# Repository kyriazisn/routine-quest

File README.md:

# Routine Quest

Παιδικό device (4 φυσικά κουμπιά, ESP32-S3, Wi-Fi) που μετατρέπει τις καθημερινές ρουτίνες σε quests και ειδοποιεί τον γονέα.

## Δομή

| Φάκελος | Περιεχόμενο |
|---|---|
| `docs/` | Product brief, game design, test plan, risks |
| `firmware/` | ESP32-S3 firmware (ESP-IDF) |
| `backend/` | FastAPI + Postgres, device & parent API, Web Push |
| `app/` | Parent PWA |
| `hardware/` | KiCad schematic, BOM, PCB |

## Ροή εργασίας

- Κάθε αλλαγή σε ξεχωριστό branch → PR → review → merge στο `main`.
- Κανένα direct commit στο `main` μετά το initial scaffold.
- Το PCB layout ξεκινά **μόνο** μετά από έγκριση του schematic.

## Φάσεις

1. Product brief & user stories — `docs/01-product-brief.md`
2. Game loop, XP, streaks, rewards — `docs/02-game-design.md`
3. Wireframes (Figma)
4. Firmware — `firmware/`
5. Backend & notifications — `docs/05-backend.md`
6. Schematic → (έγκριση) → PCB — `docs/06-hardware.md`
6.5. Parent PWA: υλοποίηση των wireframes, Web Push, BLE provisioning + claim (`app/`)
7. Test plan (end-to-end: device + backend + PWA)
8. Landing page & launch
9. Risks, safety, privacy, parental controls

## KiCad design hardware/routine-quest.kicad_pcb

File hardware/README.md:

# Routine Quest — Hardware

Design notes, calculations and the approval checklist: [`docs/06-hardware.md`](../docs/06-hardware.md).

> **Status:** schematic v0.1 approved (2026-10-13). PCB layout (Phase 6b) **in progress, not for ordering** — see [`docs/06b-pcb.md`](../docs/06b-pcb.md).

## Files

| Path | |
|---|---|
| `routine-quest.kicad_pro` / `routine-quest.kicad_sch` | Main board |
| `button-board/button-board.kicad_sch` | Button board (×4) |
| `bom/*.csv` | Bill of materials |
| `build/*.pdf` | Review renders (generated, not committed — see CI artifact) |
| `build/*.netlist.json` | Reviewed netlist, checked against the schematic |
| `tools/gen_schematics.py` | **Source of truth.** Edit this, not the `.kicad_sch` |
| `tools/check_schematic.py` | Independent connectivity + ERC-style checks |
| `tools/render_schematic.py` | PDF/PNG render without KiCad |

## Regenerate & check

```bash
git clone https://github.com/espressif/kicad-libraries.git /tmp/esplib   # pinned SHA in .github/workflows/hardware.yml
pip install kiutils==1.4.8 matplotlib
ESP_KICAD_LIB=/tmp/esplib/symbols/Espressif.kicad_sym python hardware/tools/gen_schematics.py
python hardware/tools/check_schematic.py
python hardware/tools/render_schematic.py
```

Then run KiCad's own ERC (`kicad-cli sch erc`) — see docs/06 §7.

## Licences

The ESP32-S3-WROOM-1 symbol embedded in the schematic comes from
[espressif/kicad-libraries](https://github.com/espressif/kicad-libraries) (CC-BY-SA 4.0 with the KiCad library
exception for designs).

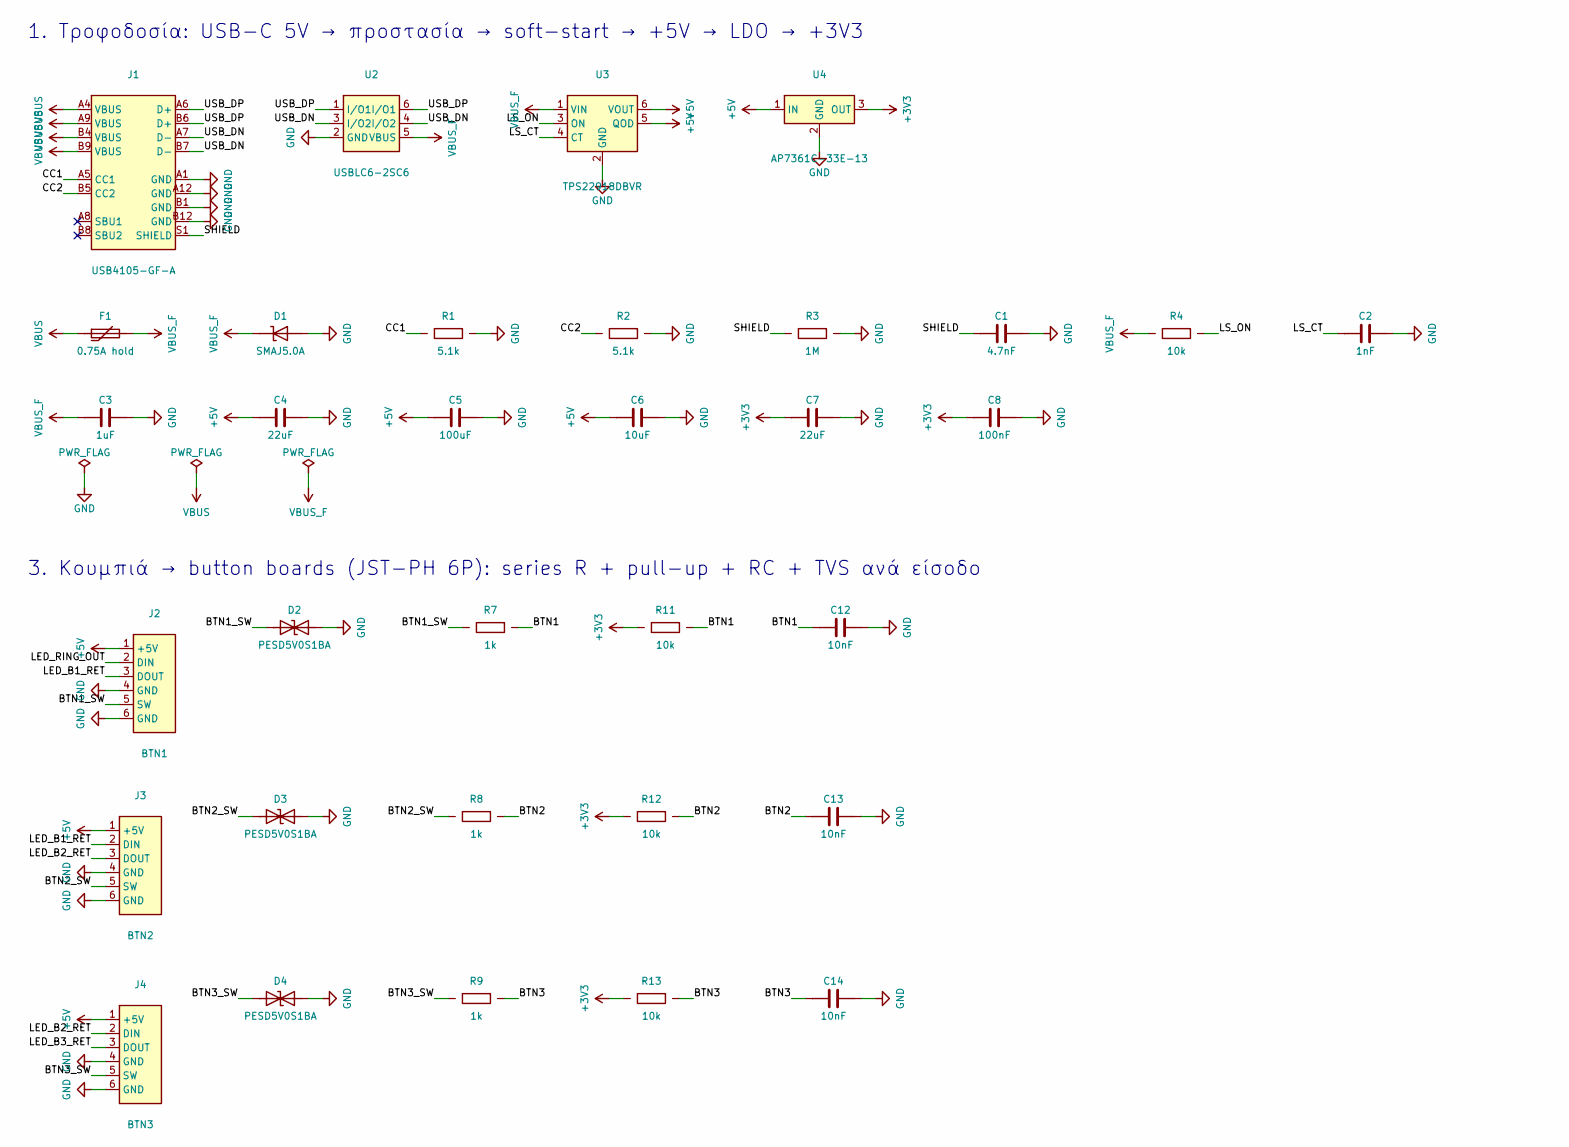
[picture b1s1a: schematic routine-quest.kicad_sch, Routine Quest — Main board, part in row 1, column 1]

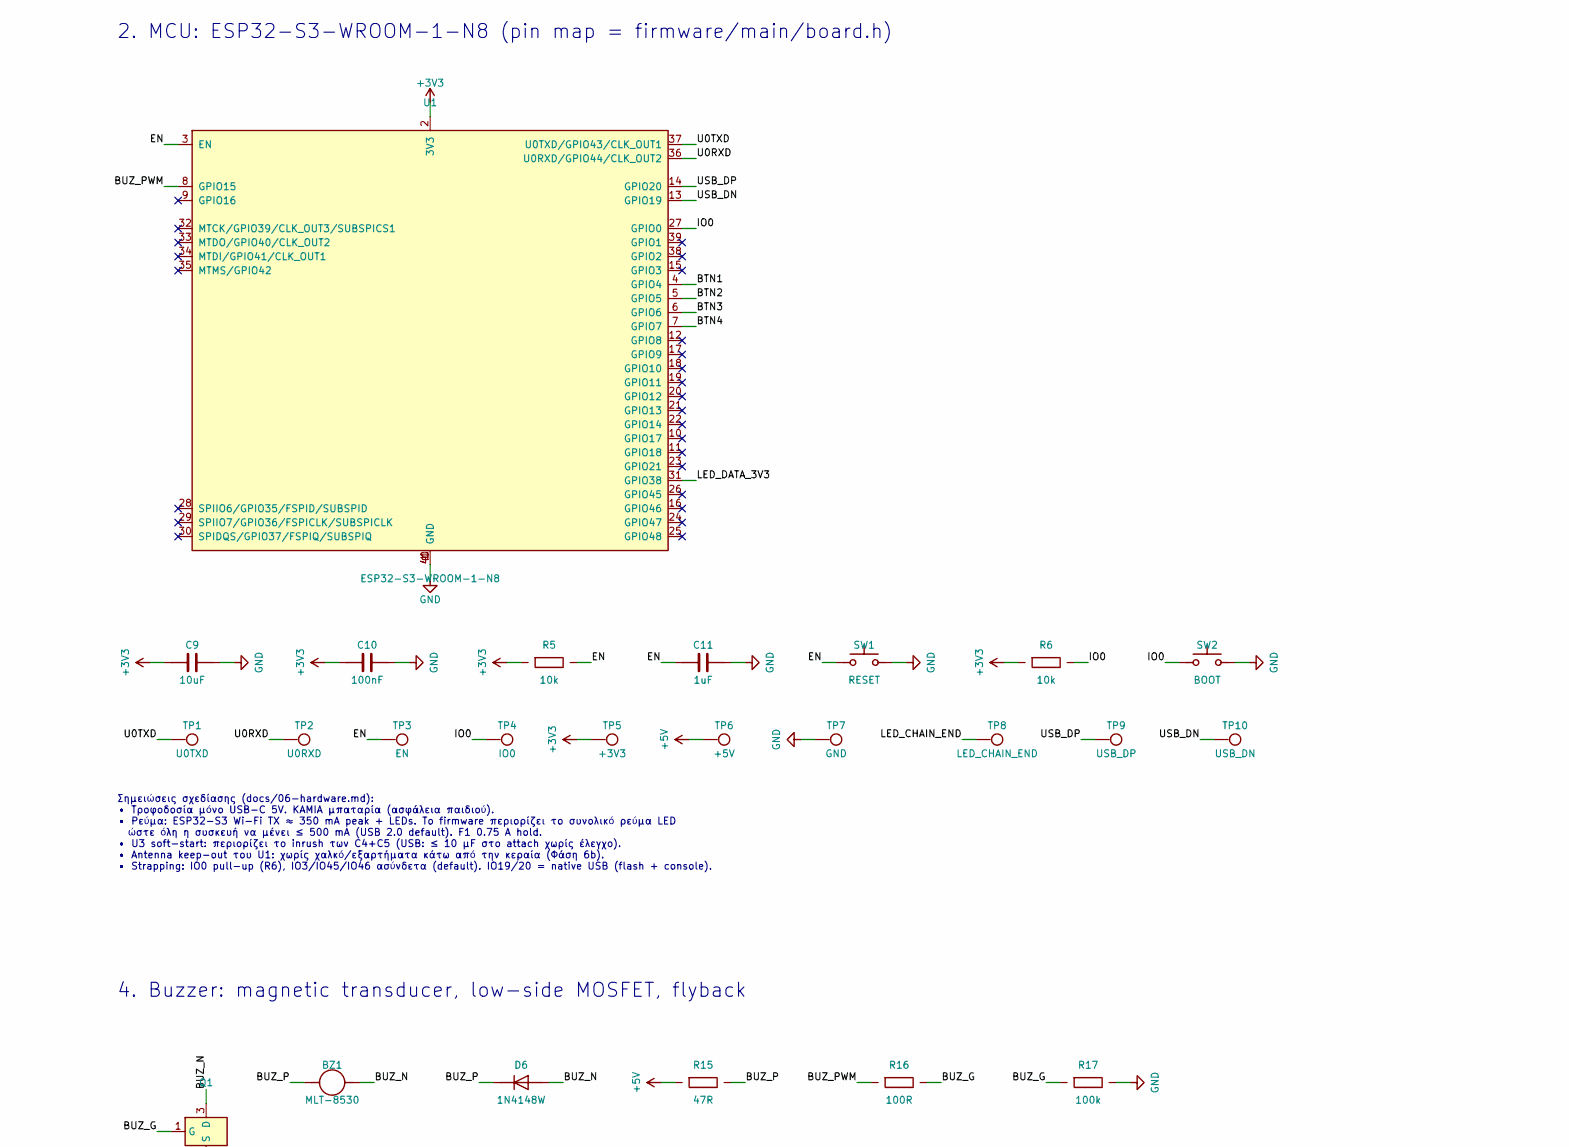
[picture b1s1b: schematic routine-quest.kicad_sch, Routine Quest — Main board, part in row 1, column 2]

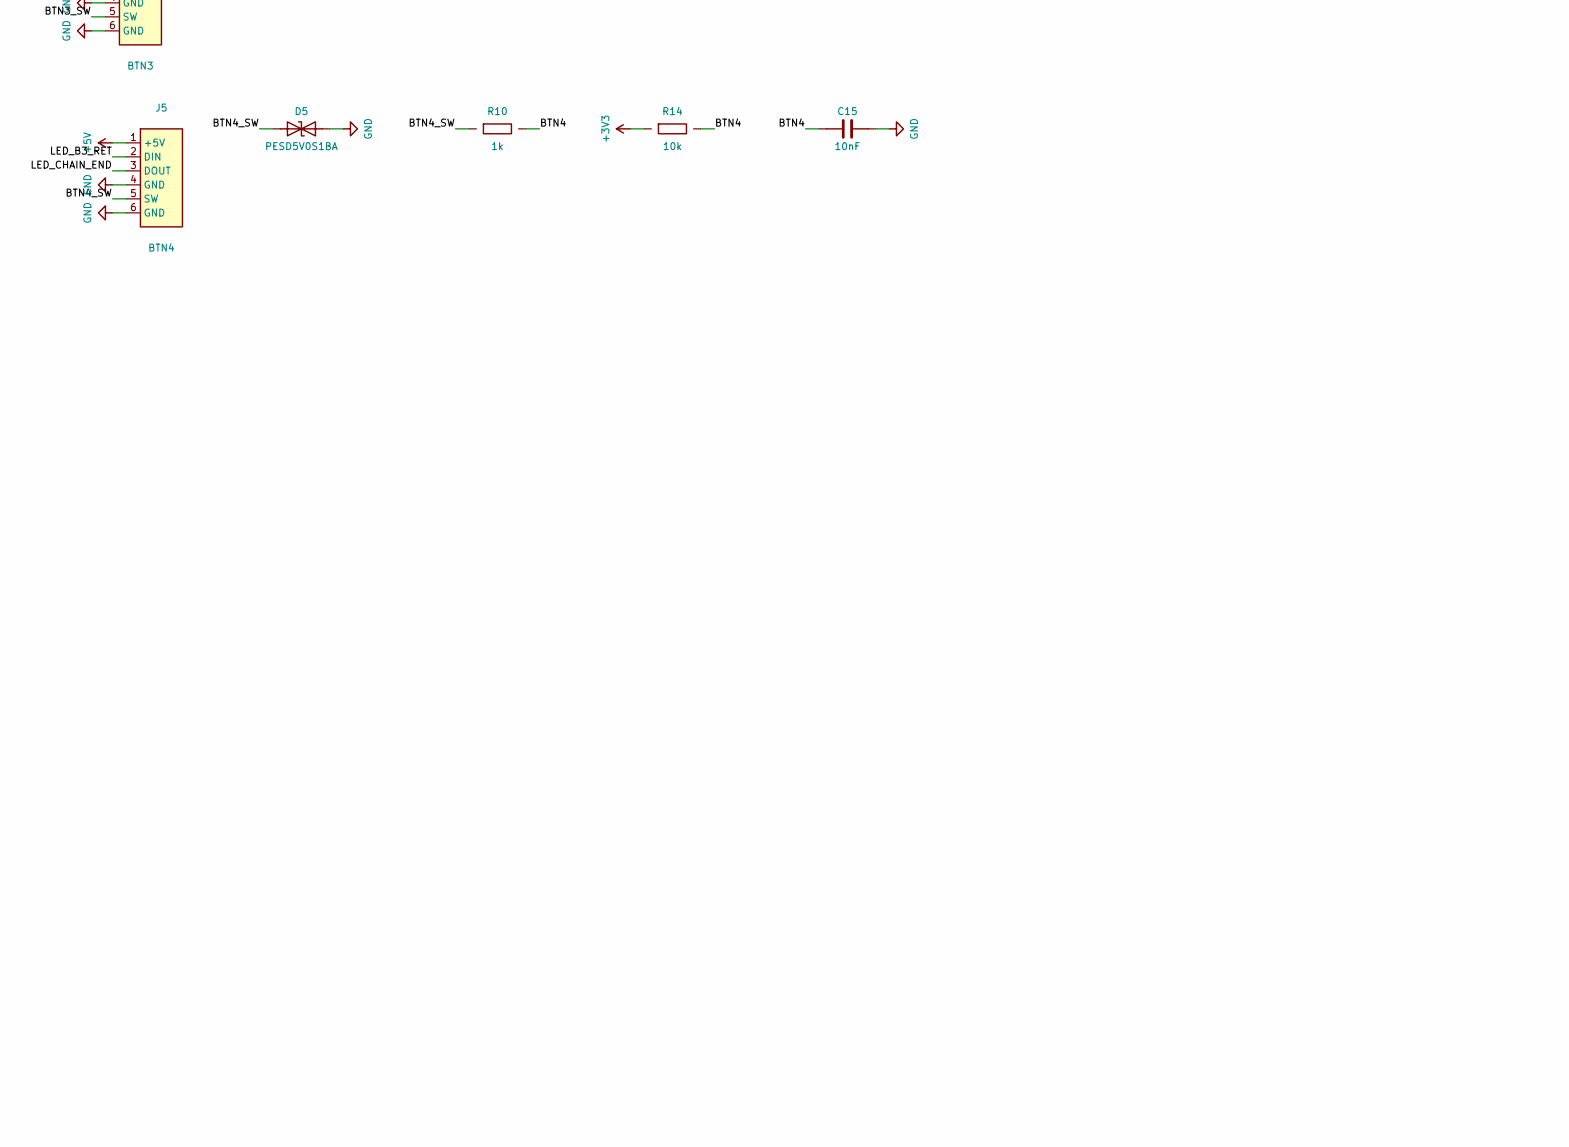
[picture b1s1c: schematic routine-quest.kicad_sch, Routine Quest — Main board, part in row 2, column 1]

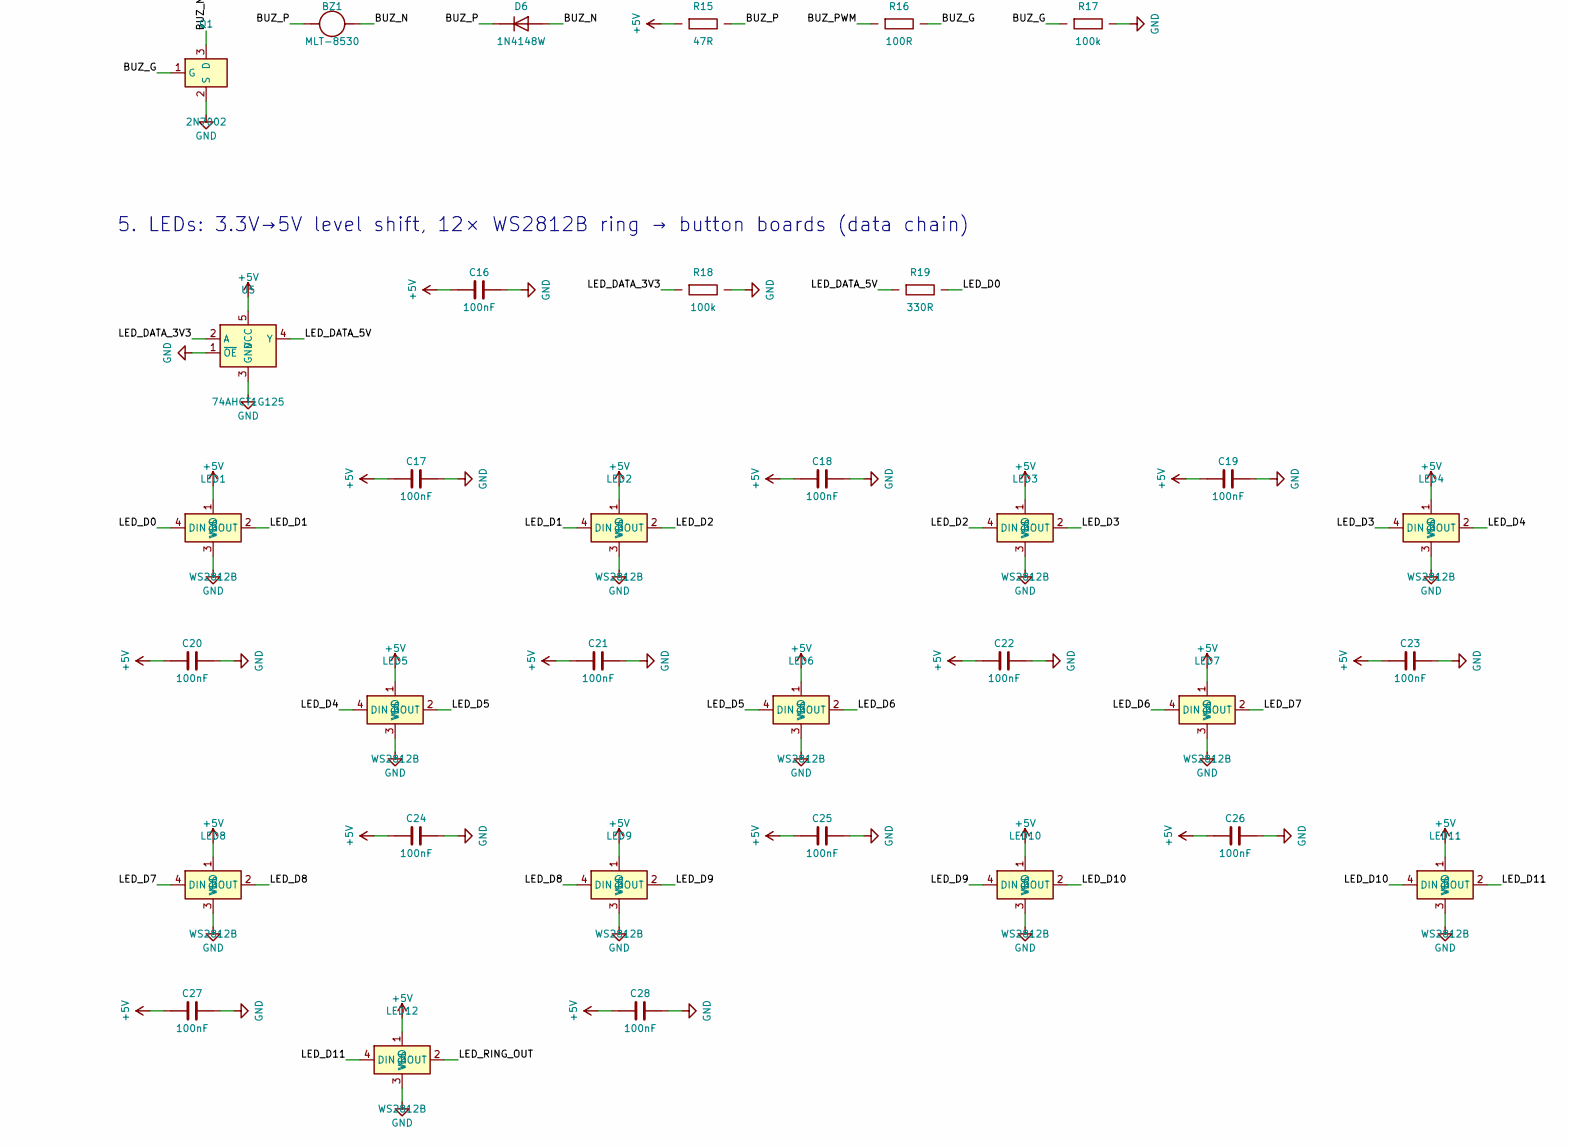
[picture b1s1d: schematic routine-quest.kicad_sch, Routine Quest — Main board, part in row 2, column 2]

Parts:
BZ1: MLT-8530; Buzzer_MLT-8530; MPN MLT-8530
C1: 4.7nF; C_0603_1608Metric
C2: 1nF; C_0603_1608Metric
C3, C11: 1uF; C_0603_1608Metric
C4, C7: 22uF; C_0805_2012Metric
C5: 100uF; C_1210_3225Metric
C6, C9: 10uF; C_0805_2012Metric
C8, C10, C16, C17, C18, C19, C20, C21, C22, C23, C24, C25, C26, C27, C28: 100nF; C_0603_1608Metric
C12, C13, C14, C15: 10nF; C_0603_1608Metric
D1: SMAJ5.0A; D_SMA; MPN SMAJ5.0A
D2, D3, D4, D5: PESD5V0S1BA; D_SOD-323; MPN PESD5V0S1BA,115
D6: 1N4148W; D_SOD-123; MPN 1N4148W
F1: 0.75A hold; Fuse_1812_4532Metric; MPN MF-MSMF075-2
J1: USB4105-GF-A; USB_C_Receptacle_GCT_USB4105-xx-A_16P_TopMnt_Horizontal; MPN USB4105-GF-A
J2: BTN1; JST_PH_B6B-PH-K_1x06_P2.00mm_Vertical; MPN B6B-PH-K-S(LF)(SN)
J3: BTN2; JST_PH_B6B-PH-K_1x06_P2.00mm_Vertical; MPN B6B-PH-K-S(LF)(SN)
J4: BTN3; JST_PH_B6B-PH-K_1x06_P2.00mm_Vertical; MPN B6B-PH-K-S(LF)(SN)
J5: BTN4; JST_PH_B6B-PH-K_1x06_P2.00mm_Vertical; MPN B6B-PH-K-S(LF)(SN)
LED1, LED2, LED3, LED4, LED5, LED6, LED7, LED8, LED9, LED10, LED11, LED12: WS2812B; LED_WS2812B_PLCC4_5.0x5.0mm_P3.2mm; MPN WS2812B-B/W
Q1: 2N7002; SOT-23; MPN 2N7002
R1, R2: 5.1k; R_0603_1608Metric
R3: 1M; R_0603_1608Metric
R4, R5, R6, R11, R12, R13, R14: 10k; R_0603_1608Metric
R7, R8, R9, R10: 1k; R_0603_1608Metric
R15: 47R; R_1206_3216Metric
R16: 100R; R_0603_1608Metric
R17, R18: 100k; R_0603_1608Metric
R19: 330R; R_0603_1608Metric
SW1: RESET; SW_SPST_TL3342; MPN TL3342F160QG
SW2: BOOT; SW_SPST_TL3342; MPN TL3342F160QG
TP1: U0TXD; TestPoint_Pad_D1.5mm
TP2: U0RXD; TestPoint_Pad_D1.5mm
TP3: EN; TestPoint_Pad_D1.5mm
TP4: IO0; TestPoint_Pad_D1.5mm
TP5: +3V3; TestPoint_Pad_D1.5mm
TP6: +5V; TestPoint_Pad_D1.5mm
TP7: GND; TestPoint_Pad_D1.5mm
TP8: LED_CHAIN_END; TestPoint_Pad_D1.5mm
TP9: USB_DP; TestPoint_Pad_D1.5mm
TP10: USB_DN; TestPoint_Pad_D1.5mm
U1: ESP32-S3-WROOM-1-N8; ESP32-S3-WROOM-1; MPN ESP32-S3-WROOM-1-N8
U2: USBLC6-2SC6; SOT-23-6; MPN USBLC6-2SC6
U3: TPS22918DBVR; SOT-23-6; MPN TPS22918DBVR
U4: AP7361C-33E-13; SOT-223-3_TabPin2; MPN AP7361C-33E-13
U5: 74AHCT1G125; SOT-23-5; MPN SN74AHCT1G125DBVR

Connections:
+3V3: C7.1, C8.1, C9.1, C10.1, R5.1, R6.1, R11.1, R12.1, R13.1, R14.1, TP5.1, U1.2 (3V3), U4.3 (OUT)
+5V: C4.1, C5.1, C6.1, C16.1, C17.1, C18.1, C19.1, C20.1, C21.1, C22.1, C23.1, C24.1, C25.1, C26.1, C27.1, C28.1, J2.1 (+5V), J3.1 (+5V), J4.1 (+5V), J5.1 (+5V), LED1.1 (VDD), LED2.1 (VDD), LED3.1 (VDD), LED4.1 (VDD), LED5.1 (VDD), LED6.1 (VDD), LED7.1 (VDD), LED8.1 (VDD), LED9.1 (VDD), LED10.1 (VDD), LED11.1 (VDD), LED12.1 (VDD), R15.1, TP6.1, U3.5 (QOD), U3.6 (VOUT), U4.1 (IN), U5.5 (VCC)
BTN1: C12.1, R7.2, R11.2, U1.4 (GPIO4)
BTN1_SW: D2.1 (A1), J2.5 (SW), R7.1
BTN2: C13.1, R8.2, R12.2, U1.5 (GPIO5)
BTN2_SW: D3.1 (A1), J3.5 (SW), R8.1
BTN3: C14.1, R9.2, R13.2, U1.6 (GPIO6)
BTN3_SW: D4.1 (A1), J4.5 (SW), R9.1
BTN4: C15.1, R10.2, R14.2, U1.7 (GPIO7)
BTN4_SW: D5.1 (A1), J5.5 (SW), R10.1
BUZ_G: Q1.1 (G), R16.2, R17.1
BUZ_N: BZ1.2 (-), D6.2 (A), Q1.3 (D)
BUZ_P: BZ1.1 (+), D6.1 (K), R15.2
BUZ_PWM: R16.1, U1.8 (GPIO15)
CC1: J1.A5 (CC1), R1.1
CC2: J1.B5 (CC2), R2.1
EN: C11.1, R5.2, SW1.1, TP3.1, U1.3 (EN)
GND: C1.2, C2.2, C3.2, C4.2, C5.2, C6.2, C7.2, C8.2, C9.2, C10.2, C11.2, C12.2, C13.2, C14.2, C15.2, C16.2, C17.2, C18.2, C19.2, C20.2, C21.2, C22.2, C23.2, C24.2, C25.2, C26.2, C27.2, C28.2, D1.2 (A), D2.2 (A2), D3.2 (A2), D4.2 (A2), D5.2 (A2), J1.A1 (GND), J1.A12 (GND), J1.B1 (GND), J1.B12 (GND), J2.4 (GND), J2.6 (GND), J3.4 (GND), J3.6 (GND), J4.4 (GND), J4.6 (GND), J5.4 (GND), J5.6 (GND), LED1.3 (VSS), LED2.3 (VSS), LED3.3 (VSS), LED4.3 (VSS), LED5.3 (VSS), LED6.3 (VSS), LED7.3 (VSS), LED8.3 (VSS), LED9.3 (VSS), LED10.3 (VSS), LED11.3 (VSS), LED12.3 (VSS), Q1.2 (S), R1.2, R2.2, R3.2, R17.2, R18.2, SW1.2, SW2.2, TP7.1, U1.1 (GND), U1.40 (GND), U1.41 (GND), U2.2 (GND), U3.2 (GND), U4.2 (GND), U5.1 (~OE), U5.3 (GND)
IO0: R6.2, SW2.1, TP4.1, U1.27 (GPIO0)
LED_B1_RET: J2.3 (DOUT), J3.2 (DIN)
LED_B2_RET: J3.3 (DOUT), J4.2 (DIN)
LED_B3_RET: J4.3 (DOUT), J5.2 (DIN)
LED_CHAIN_END: J5.3 (DOUT), TP8.1
LED_D0: LED1.4 (DIN), R19.2
LED_D1: LED1.2 (DOUT), LED2.4 (DIN)
LED_D2: LED2.2 (DOUT), LED3.4 (DIN)
LED_D3: LED3.2 (DOUT), LED4.4 (DIN)
LED_D4: LED4.2 (DOUT), LED5.4 (DIN)
LED_D5: LED5.2 (DOUT), LED6.4 (DIN)
LED_D6: LED6.2 (DOUT), LED7.4 (DIN)
LED_D7: LED7.2 (DOUT), LED8.4 (DIN)
LED_D8: LED8.2 (DOUT), LED9.4 (DIN)
LED_D9: LED9.2 (DOUT), LED10.4 (DIN)
LED_D10: LED10.2 (DOUT), LED11.4 (DIN)
LED_D11: LED11.2 (DOUT), LED12.4 (DIN)
LED_DATA_3V3: R18.1, U1.31 (GPIO38), U5.2 (A)
LED_DATA_5V: R19.1, U5.4 (Y)
LED_RING_OUT: J2.2 (DIN), LED12.2 (DOUT)
LS_CT: C2.1, U3.4 (CT)
LS_ON: R4.2, U3.3 (ON)
SHIELD: C1.1, J1.S1 (SHIELD), R3.1
U0RXD: TP2.1, U1.36 (U0RXD/GPIO44/CLK_OUT2)
U0TXD: TP1.1, U1.37 (U0TXD/GPIO43/CLK_OUT1)
USB_DN: J1.A7 (D-), J1.B7 (D-), TP10.1, U1.13 (GPIO19), U2.3 (I/O2), U2.4 (I/O2)
USB_DP: J1.A6 (D+), J1.B6 (D+), TP9.1, U1.14 (GPIO20), U2.1 (I/O1), U2.6 (I/O1)
VBUS: F1.1, J1.A4 (VBUS), J1.A9 (VBUS), J1.B4 (VBUS), J1.B9 (VBUS)
VBUS_F: C3.1, D1.1 (K), F1.2, R4.1, U2.5 (VBUS), U3.1 (VIN)

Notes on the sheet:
1. Τροφοδοσία: USB-C 5V → προστασία → soft-start → +5V → LDO → +3V3
2. MCU: ESP32-S3-WROOM-1-N8 (pin map = firmware/main/board.h)
3. Κουμπιά → button boards (JST-PH 6P): series R + pull-up + RC + TVS ανά είσοδο
Σημειώσεις σχεδίασης (docs/06-hardware.md): • Τροφοδοσία μόνο USB-C 5V. ΚΑΜΙΑ μπαταρία (ασφάλεια παιδιού). • Ρεύμα: ESP32-S3 Wi-Fi TX ≈ 350 mA peak + LEDs. Το firmware περιορίζει το συνολικό ρεύμα LED ώστε όλη η συσκευή να μένει ≤ 500 mA (USB 2.0 default). F1 0.75 A hold. • U3 soft-start: περιορίζε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
4. Buzzer: magnetic transducer, low-side MOSFET, flyback
5. LEDs: 3.3V→5V level shift, 12× WS2812B ring → button boards (data chain)

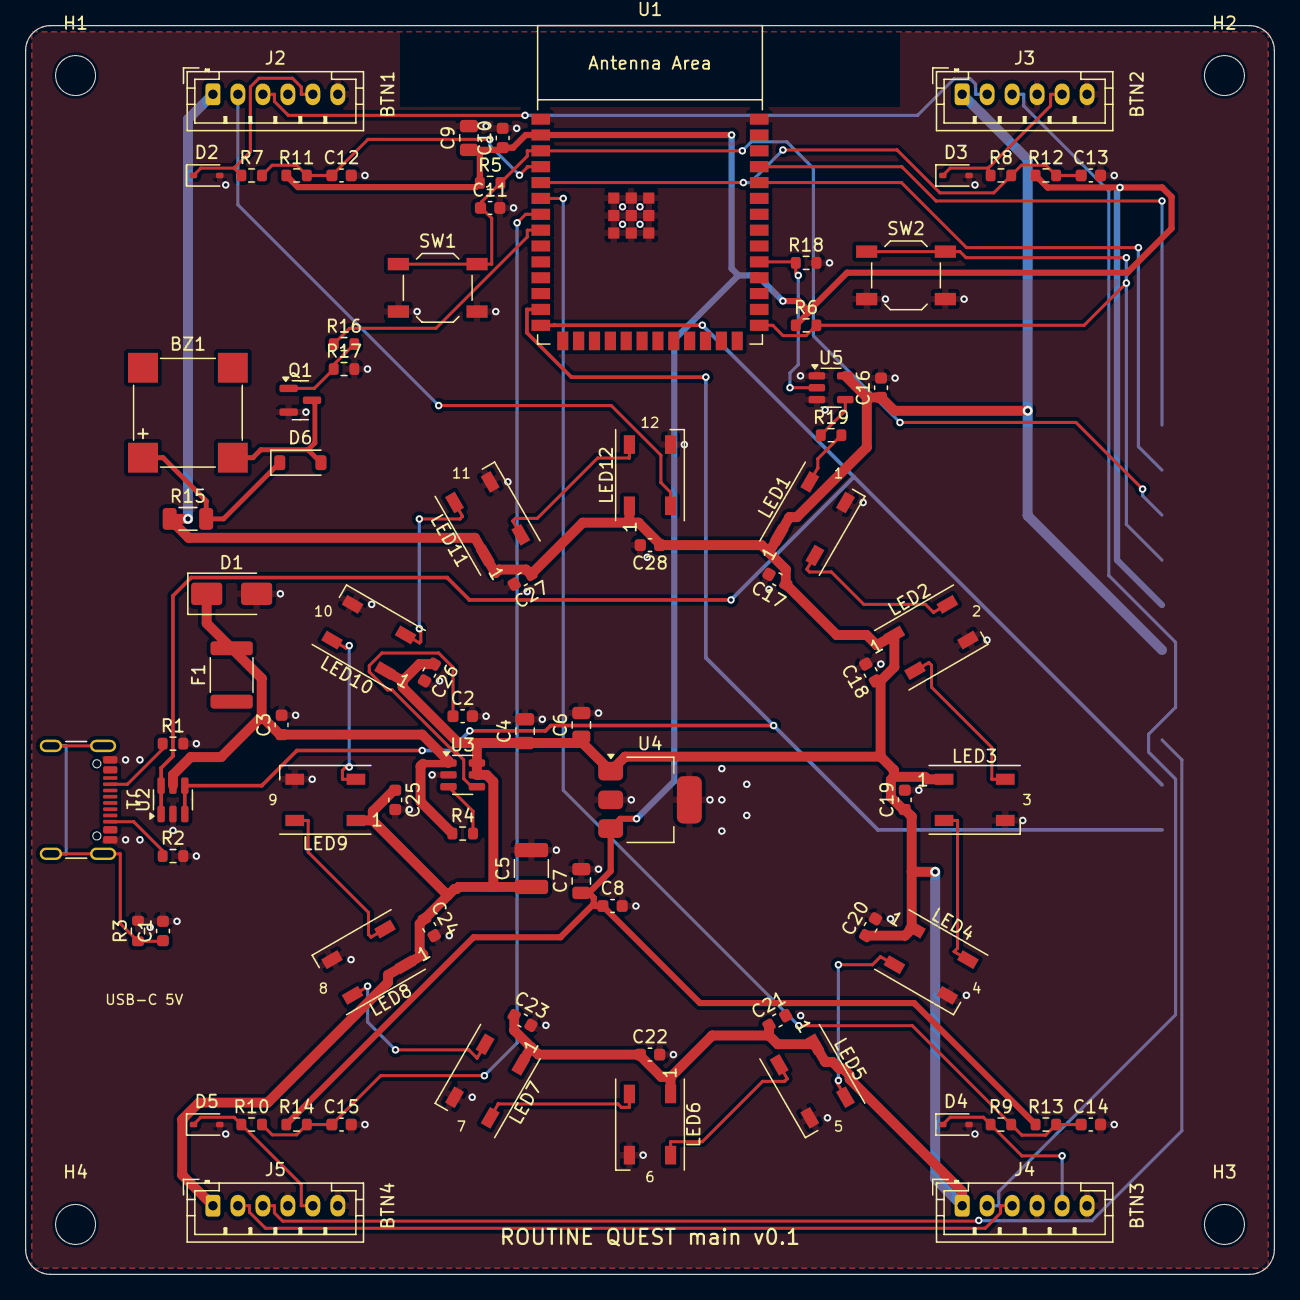
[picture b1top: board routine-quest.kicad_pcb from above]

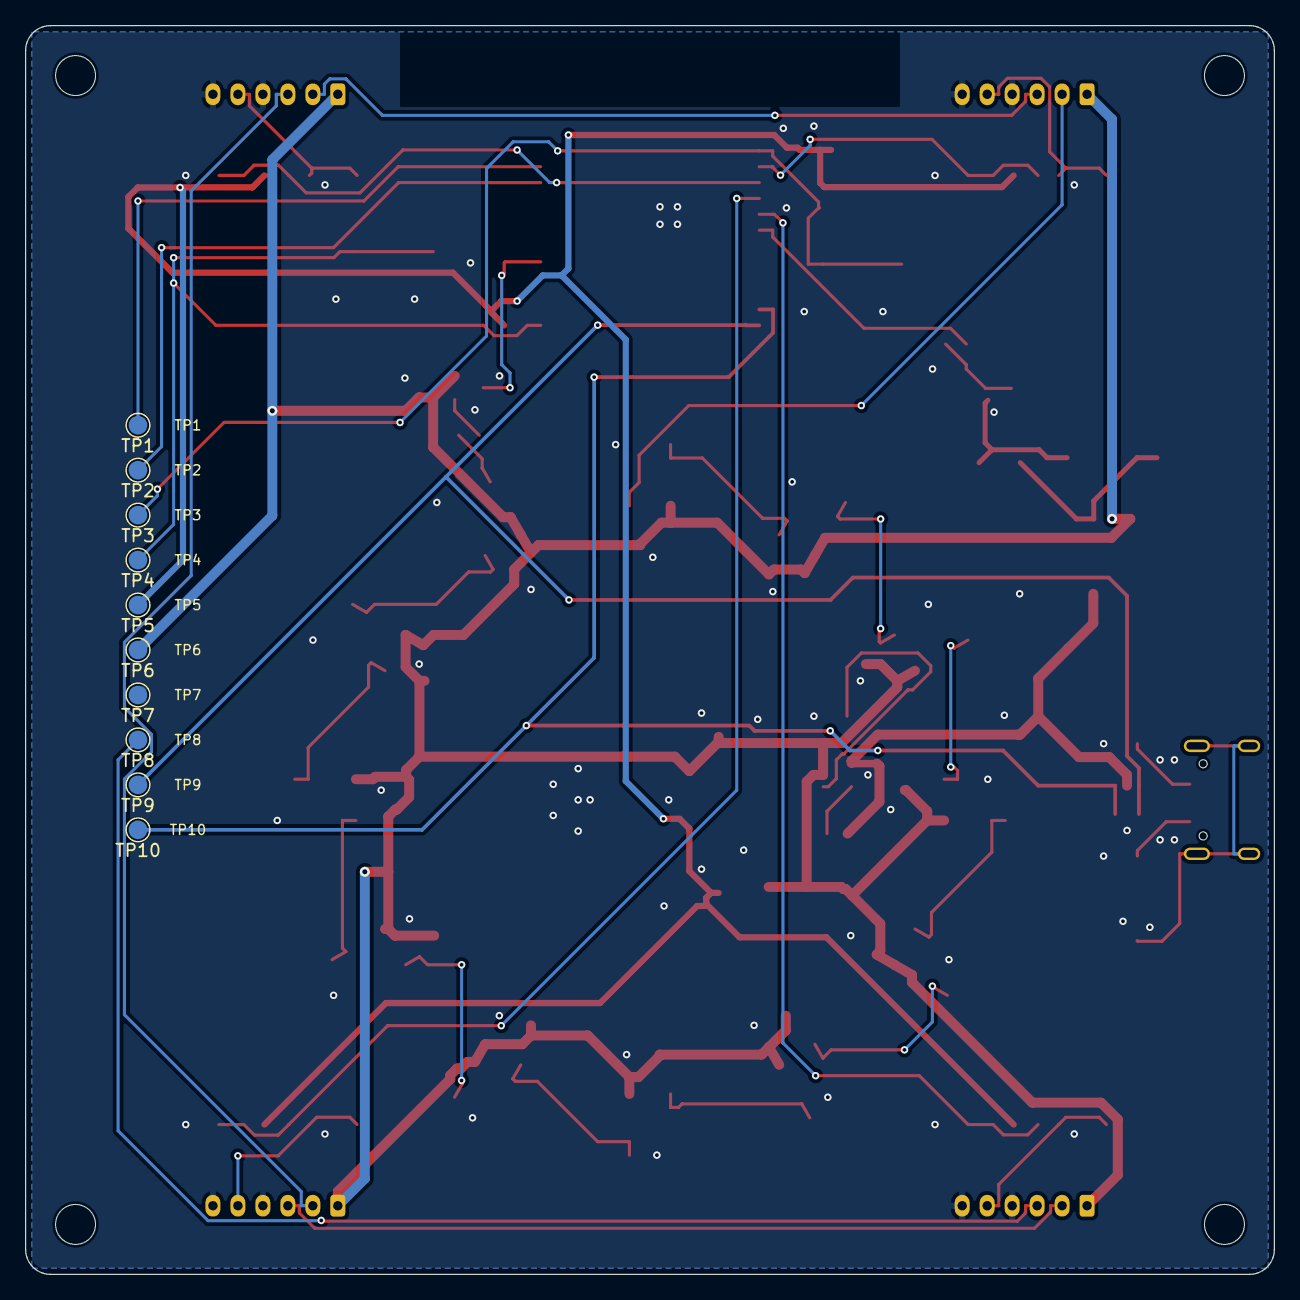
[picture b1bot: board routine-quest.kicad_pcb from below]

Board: 2 copper layers, 100.0 x 100.0 mm, 94 parts (10 on the bottom side), 47 nets.

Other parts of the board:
H1, H2, H3, H4: MountingHole; MountingHole_3.2mm_M3

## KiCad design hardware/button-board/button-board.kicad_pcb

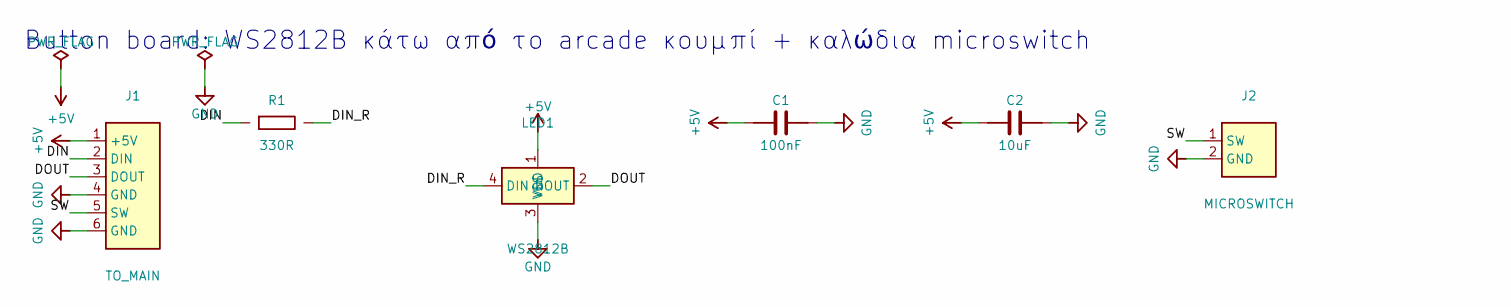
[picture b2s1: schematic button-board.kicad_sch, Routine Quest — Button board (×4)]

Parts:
C1: 100nF; C_0603_1608Metric
C2: 10uF; C_0805_2012Metric
J1: TO_MAIN; JST_PH_B6B-PH-K_1x06_P2.00mm_Vertical; MPN B6B-PH-K-S(LF)(SN)
J2: MICROSWITCH; JST_PH_B2B-PH-K_1x02_P2.00mm_Vertical; MPN B2B-PH-K-S(LF)(SN)
LED1: WS2812B; LED_WS2812B_PLCC4_5.0x5.0mm_P3.2mm; MPN WS2812B-B/W
R1: 330R; R_0603_1608Metric

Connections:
+5V: C1.1, C2.1, J1.1 (+5V), LED1.1 (VDD)
DIN: J1.2 (DIN), R1.1
DIN_R: LED1.4 (DIN), R1.2
DOUT: J1.3 (DOUT), LED1.2 (DOUT)
GND: C1.2, C2.2, J1.4 (GND), J1.6 (GND), J2.2 (GND), LED1.3 (VSS)
SW: J1.5 (SW), J2.1 (SW)

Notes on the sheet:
Button board: WS2812B κάτω από το arcade κουμπί + καλώδια microswitch

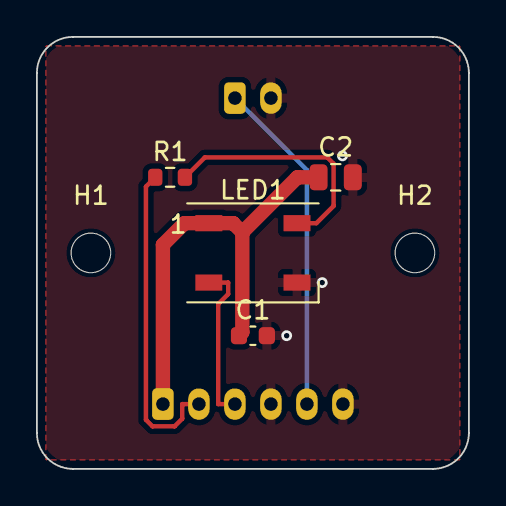
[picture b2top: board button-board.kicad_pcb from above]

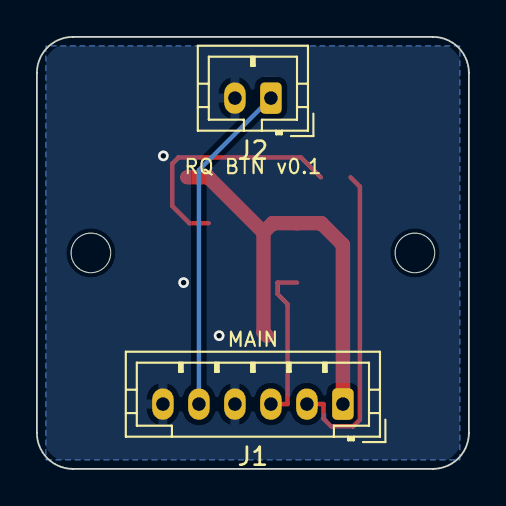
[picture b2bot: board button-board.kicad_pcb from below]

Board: 2 copper layers, 24.0 x 24.0 mm, 8 parts (2 on the bottom side), 6 nets.

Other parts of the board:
H1, H2: MountingHole; MountingHole_2.2mm_M2
